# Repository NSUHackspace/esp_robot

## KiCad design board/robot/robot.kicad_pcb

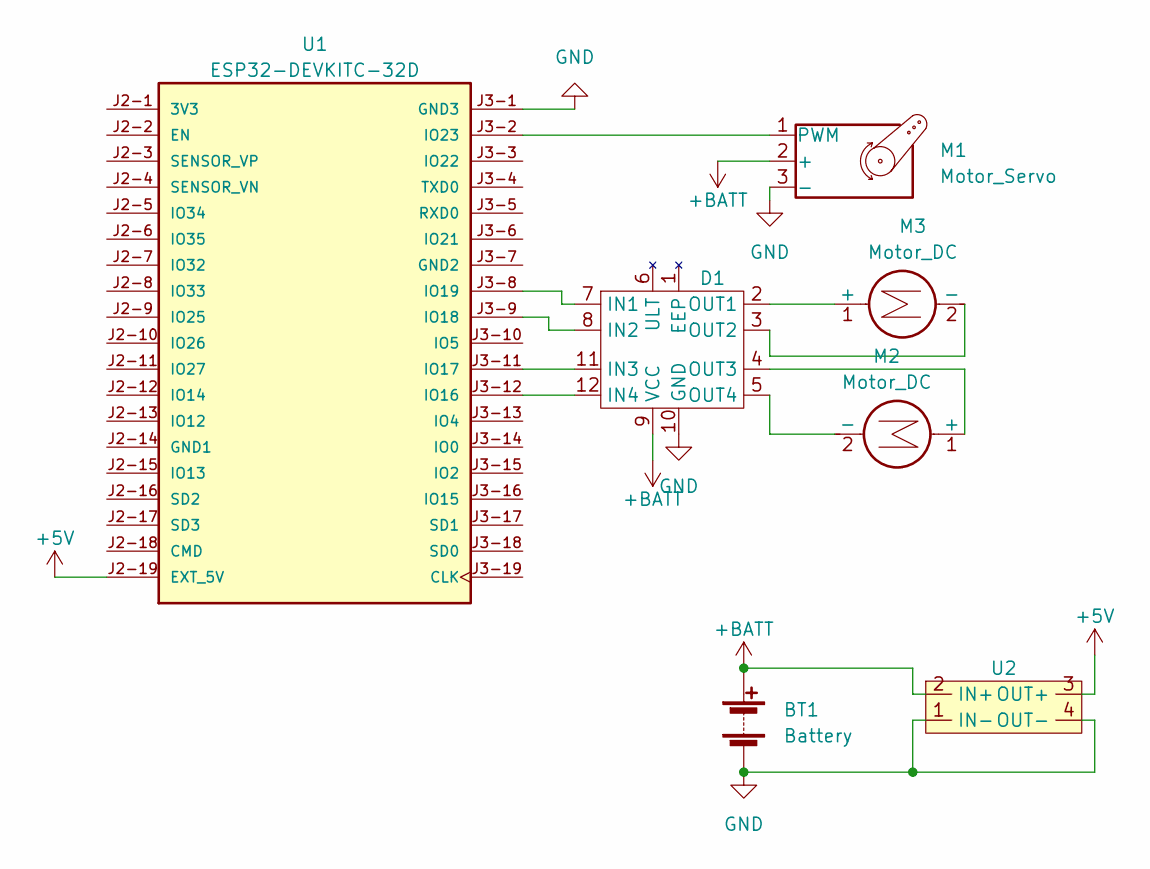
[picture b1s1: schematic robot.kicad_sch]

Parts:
BT1: Battery; TerminalBlock_bornier-2_P5.08mm
D1: DIP-12_600
M1: Motor_Servo; PinHeader_1x03_P2.54mm_Vertical
M2, M3: Motor_DC; TerminalBlock_bornier-2_P5.08mm
U1: ESP32-DEVKITC-32D; MODULE_ESP32-DEVKITC-32D; PARTREV V4
U2: DIP-4_600

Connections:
+5V: U1.J2-19 (EXT_5V), U2.3 (OUT+)
+BATT: BT1.1 (+), D1.9 (VCC), M1.2 (+), U2.2 (IN+)
GND: BT1.2 (-), D1.10 (GND), M1.3 (-), U1.J3-1 (GND3), U2.1 (IN-), U2.4 (OUT-)
unnamed: D1.7 (IN1), U1.J3-8 (IO19)
unnamed: D1.8 (IN2), U1.J3-9 (IO18)
unnamed: D1.11 (IN3), U1.J3-11 (IO17)
unnamed: D1.12 (IN4), U1.J3-12 (IO16)
unnamed: D1.2 (OUT1), M3.1 (+)
unnamed: D1.3 (OUT2), M3.2 (-)
unnamed: D1.4 (OUT3), M2.1 (+)
unnamed: D1.5 (OUT4), M2.2 (-)
unnamed: M1.1 (PWM), U1.J3-2 (IO23)

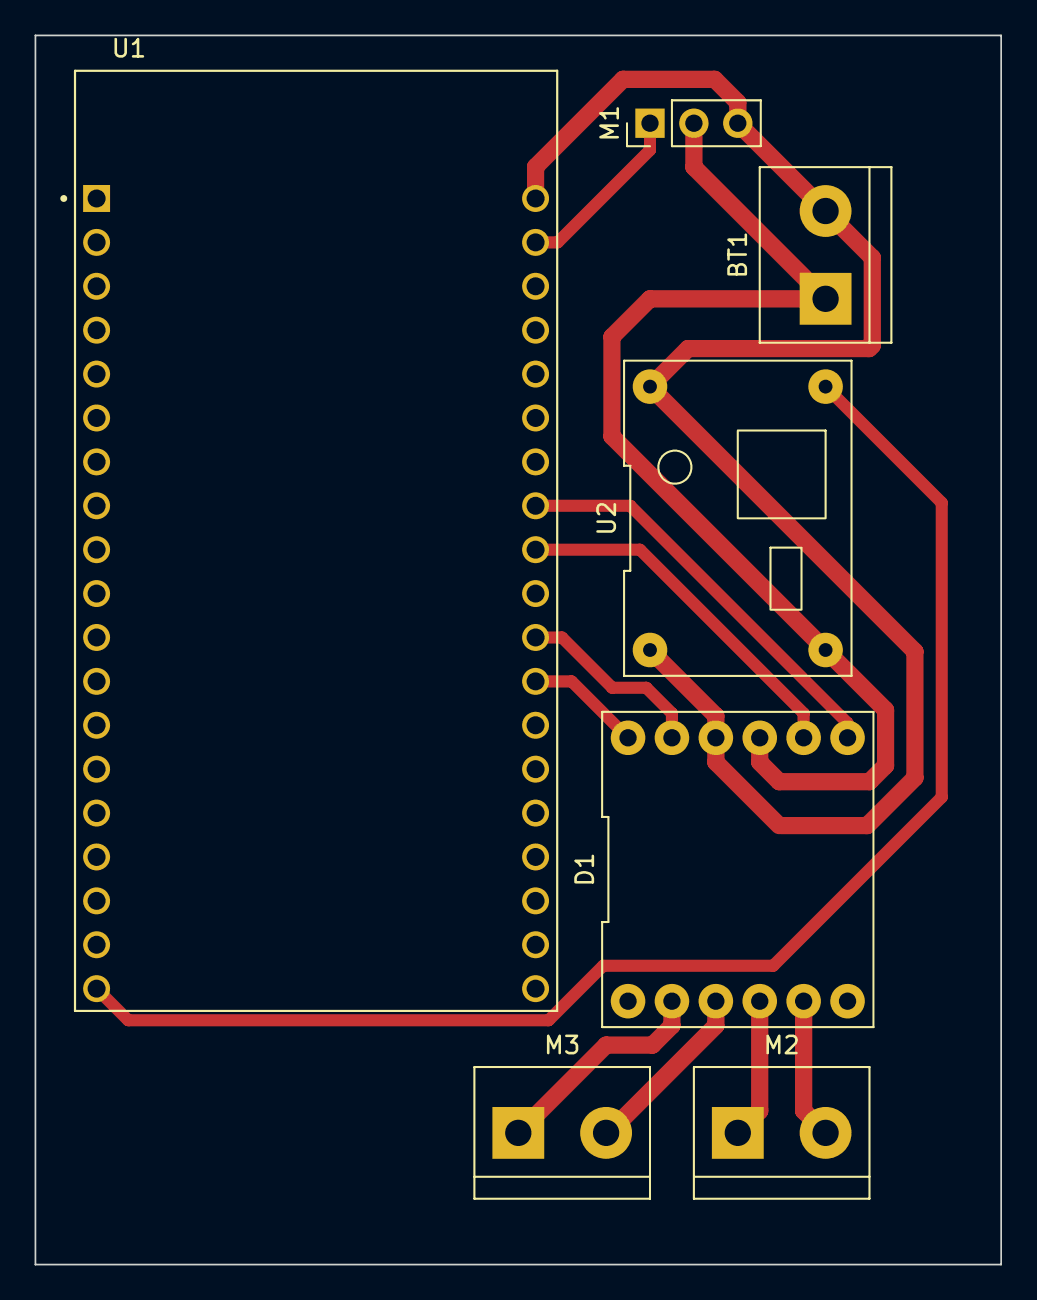
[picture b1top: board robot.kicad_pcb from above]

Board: 2 copper layers, 55.9 x 71.1 mm, 7 parts (0 on the bottom side), 12 nets.

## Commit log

2023-04-04 Fix kicad paths
2023-04-04 Fix submodule url
2023-04-04 Add sdkconfig
